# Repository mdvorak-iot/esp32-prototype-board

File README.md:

# esp32-prototype-board

EAGLE schematic for prototype board with 12V power input and all essentials.

Programmed and debugged using [ESP-PROG](https://github.com/espressif/esp-dev-kits/blob/master/esp-prog/docs/ESP-Prog_guide_en.md) interface.

## Renders

</img>

</img>

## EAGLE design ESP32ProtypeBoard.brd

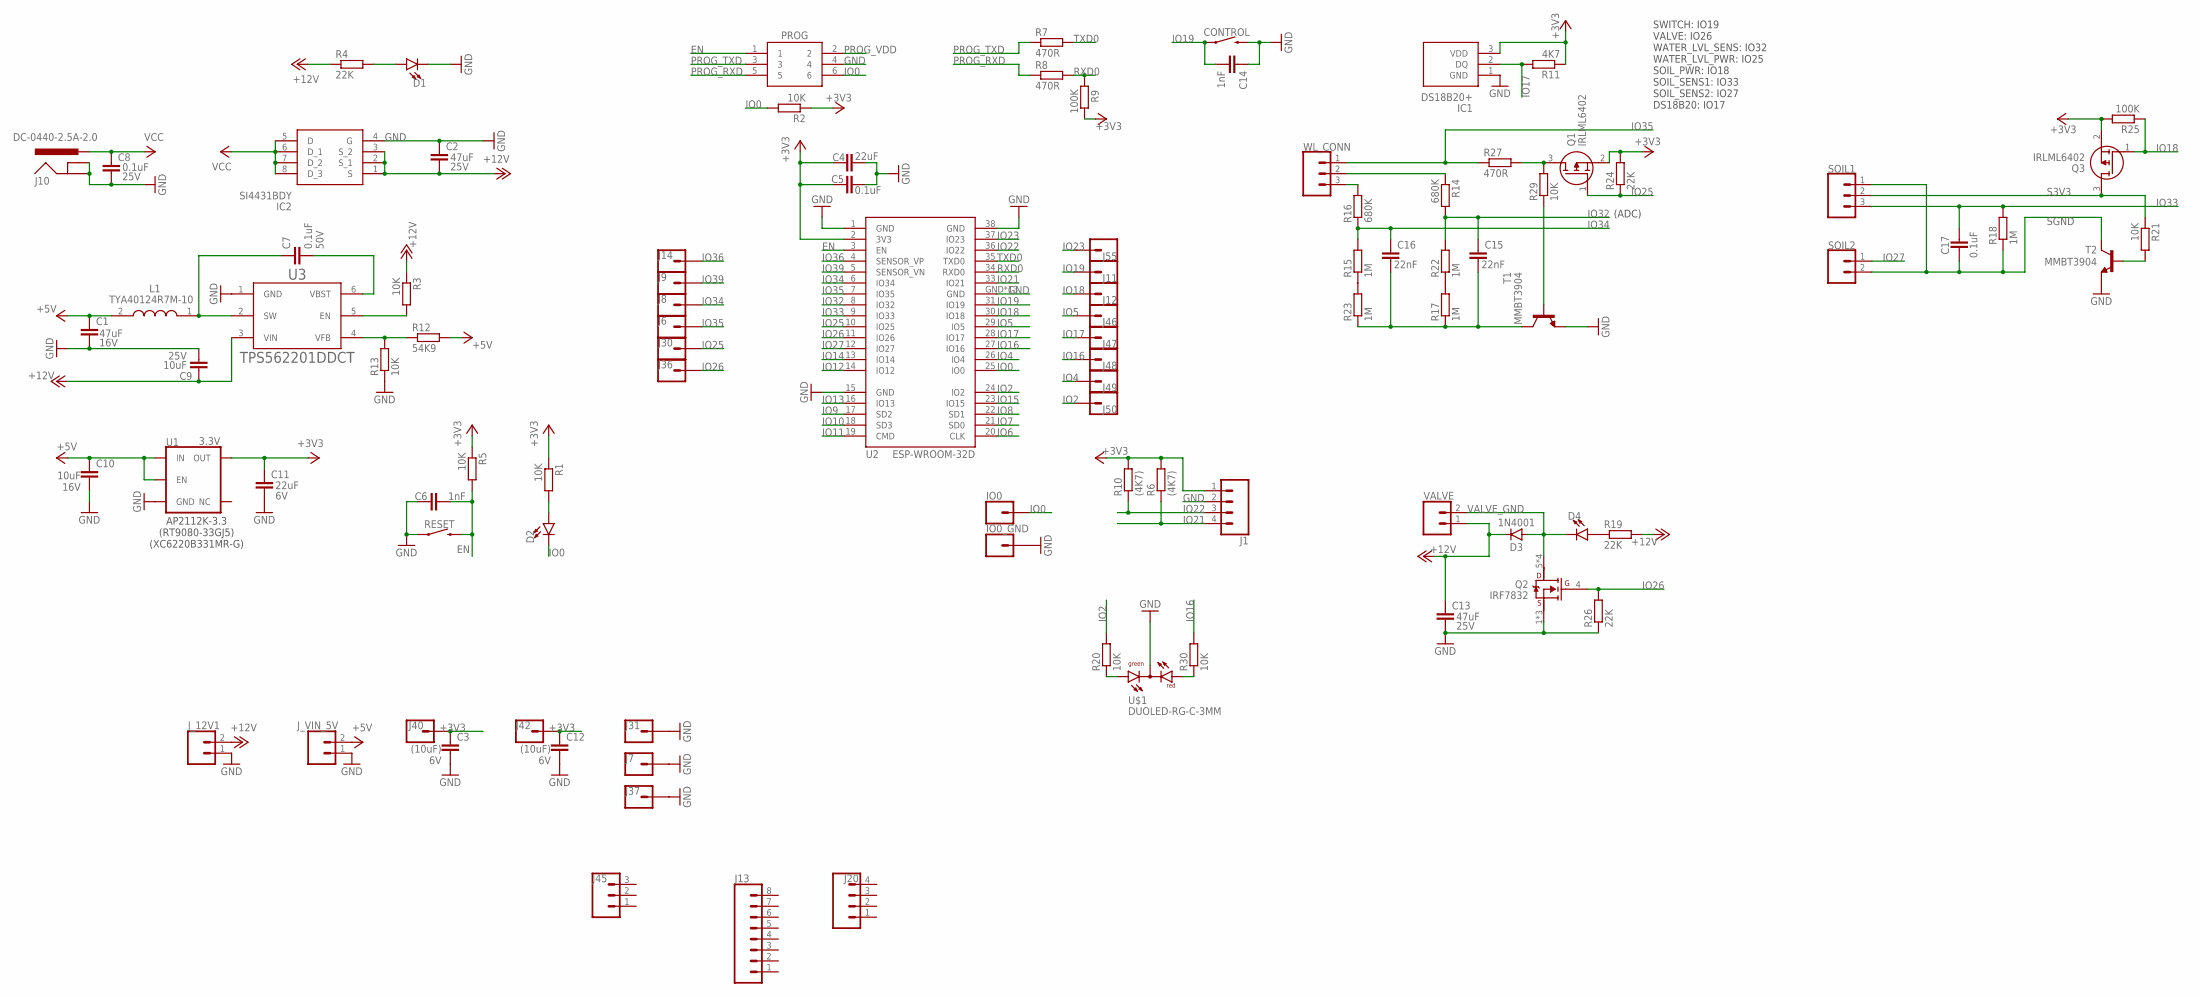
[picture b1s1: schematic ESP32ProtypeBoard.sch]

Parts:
C1: 47uF; C1206K; VOLTAGE 16V
C2, C13: 47uF; C1206K; VOLTAGE 25V
C3, C12: (10uF); C0805K; VOLTAGE 6V
C4: 22uF; C0805K
C5, C17: 0.1uF; C0805K
C6, C14: 1nF; C0805K
C7: 0.1uF; C0805K; VOLTAGE 50V
C8: 0.1uF; C0805K; VOLTAGE 25V
C9: 10uF; C0805K; VOLTAGE 25V
C10: 10uF; C0805K; VOLTAGE 16V
C11: 22uF; C0805K; VOLTAGE 6V
C15, C16: 22nF; C0805K
CONTROL: TACTILE_SIDE_SWITCH_2.5X7X3.5MM
D1: PWR; CHIPLED_0805
D2: GREEN; CHIPLED_0805
D3: 1N4001; DO41-7
D4: VALVE; LED_3MM
IC1: DS18B20+; DS18B20
IC2: SI4431BDY; SOIC127P600X175-8N
IO0: CONN_01PTH_NO_SILK_KIT; 1X01NS_KIT
IO0_GND: CONN_01PTH_NO_SILK_YES_STOP; 1X01_NO_SILK
J1: CONN_04_JSTPH_2.0MM; 1X04_JST_PH_2.0MM
J6, J7, J8, J9, J14, J30, J31, J36, J37, J40, J42: CONN_01_NO_SILK; 1X01_NO_SILK
J10: DC-0440-2.5A-2.0; DC044025A20
J11, J12, J46, J47, J48, J49, J50, J55: CONN_01PTH_NO_SILK_YES_STOP; 1X01_NO_SILK
J13: CONN_08NO_SILK_FEMALE_PTH; 1X08_NO_SILK
J20: CONN_04_NO_SILK; 1X04_NO_SILK
J45: CONN_03_NO_SILK; 1X03_NO_SILK
J_12V1: CONN_021X02_NO_SILK; 1X02_NO_SILK
J_VIN_5V: CONN_021X02_NO_SILK; 1X02_NO_SILK
L1: TYA40124R7M-10; INDPM4040X130N
PROG: DC3-06-1P27
Q1, Q3: IRLML6402; SOT95P237X112-3N
Q2: IRF7832PBF; IRF7832PBF_4
R1, R2, R3, R5, R13, R20, R21, R29, R30: 10K; R0805
R4, R19, R24, R26: 22K; R0805
R6, R10: (4K7); R0805
R7, R8, R27: 470R; R0805
R9, R25: 100K; R0805
R11: 4K7; R0805
R12: 54K9; R0805
R14, R16: 680K; R0805
R15, R17, R18, R22, R23: 1M; R0805
RESET: RESET; TACTILE_SWITCH_SMD_4X3MM
SOIL1: CONN_03_JSTXH_2.54MM_LOCK; 1X03_JST_XH_2.54MM_LOCK
SOIL2: CONN_02_JSTXH_2.54MM_LOCK; 1X02_JST_XH_2.54MM_LOCK
T1, T2: MMBT3904; SOT23-BEC
U1: 3.3V; SOT23-5
U2: ESP-WROOM-32D
U3: TPS562201DDCTTEXAS_INSTRUMENTS_TPS562201DDCT_0_0; TEXAS_INSTRUMENTS_TPS562201DDCT_0
U$1: DUOLED-RG-C-3MM; DUOLED-A-3MM
VALVE: CONN_02_JSTXH_2.54MM_LOCK; 1X02_JST_XH_2.54MM_LOCK
WL_CONN: CONN_03_JSTXH_2.54MM_LOCK; 1X03_JST_XH_2.54MM_LOCK

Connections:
+3V3: C3.1, C4.1, C5.1, C11.1, C12.1, IC1.3 (VDD), J1.1, J40.1, J42.1, Q1.2 (S), Q3.2 (S), R1.1, R2.1, R5.1, R6.2, R9.1, R10.2, R11.1, R24.2, R25.2, U1.5 (OUT), U2.2 (3V3)
+5V: C1.1, C10.1, J_VIN_5V.2, L1.2, R12.2, U1.1 (IN), U1.3 (EN)
+12V: C2.2, C9.1, C13.1, D3.C, IC2.1 (S), IC2.2 (S_1), IC2.3 (S_2), J_12V1.2, R3.1, R4.1, R19.2, U3.3 (VIN), VALVE.1
D2A: D2.A, R1.2
EN: C6.2, PROG.1, R5.2, RESET.2, U2.3 (EN)
GND: C1.2, C2.1, C3.2, C4.2, C5.2, C6.1, C8.2, C9.2, C10.2, C11.2, C12.2, C13.2, C14.1, CONTROL.P$2 (2), D1.C, IC1.1 (GND), IC2.4 (G), IO0_GND.1, J1.2, J7.1, J10.2 (GND), J10.3 (GNDBREAK), J31.1, J37.1, J_12V1.1, J_VIN_5V.1, PROG.4, Q2.1 (1_S), Q2.2 (1_S), Q2.3 (1_S), R13.1, R26.1, RESET.1, T1.E, T2.E, U1.2 (GND), U2.1 (GND), U2.15 (GND), U2.38 (GND), U2.GND, U2.GND_1 (GND), U2.GND_2 (GND), U2.GND_3 (GND), U2.GND_4 (GND), U2.GND_5 (GND), U2.GND_6 (GND), U2.GND_7 (GND), U2.GND_8 (GND), U2.GND_9 (GND), U2.GND_10 (GND), U2.GND_11 (GND), U2.GND_12 (GND), U3.1 (GND), U$1.2 (C)
IO0: D2.C, IO0.1, PROG.6, R2.2, U2.25 (IO0)
IO2: J50.1, R20.2, U2.24 (IO2)
IO4: J49.1, U2.26 (IO4)
IO5: J46.1, U2.29 (IO5)
IO6: U2.20 (CLK)
IO7: U2.21 (SD0)
IO8: U2.22 (SD1)
IO9: U2.17 (SD2)
IO10: U2.18 (SD3)
IO11: U2.19 (CMD)
IO12: U2.14 (IO12)
IO13: U2.16 (IO13)
IO14: U2.13 (IO14)
IO15: U2.23 (IO15)
IO16: J48.1, R30.2, U2.27 (IO16)
IO17: IC1.2 (DQ), J47.1, R11.2, U2.28 (IO17)
IO18: J12.1, Q3.1 (G), R25.1, U2.30 (IO18)
IO19: C14.2, CONTROL.P$1 (1), J11.1, U2.31 (IO19)
IO21: J1.4, R6.1, U2.33 (IO21)
IO22: J1.3, R10.1, U2.36 (IO22)
IO23: J55.1, U2.37 (IO23)
IO25: J30.1, Q1.1 (G), R24.1, U2.10 (IO25)
IO26: J36.1, Q2.4 (G), R26.2, U2.11 (IO26)
IO27: SOIL2.1, U2.12 (IO27)
IO32: C15.1, R14.2, R22.2, U2.8 (IO32)
IO33: C17.2, R18.2, SOIL1.3, U2.9 (IO33)
IO34: C16.1, J8.1, R15.2, R16.1, U2.6 (IO34)
IO35: J6.1, R27.1, U2.7 (IO35), WL_CONN.1
IO36: J14.1, U2.4 (SENSOR_VP)
IO39: J9.1, U2.5 (SENSOR_VN)
unnamed: D4.A, R19.1
unnamed: R15.1, R23.2
unnamed: R20.1, U$1.1 (AG)
unnamed: R30.1, U$1.3 (AR)
unnamed: Q1.3 (D), R27.2, R29.2
unnamed: R17.2, R22.1
unnamed: C15.2, C16.2, R17.1, R23.1, T1.C
unnamed: R21.2, T2.B
PROG_RXD: PROG.5, R8.1
PROG_TXD: PROG.3, R7.1
PROG_VDD: PROG.2
PWR_LED: D1.A, R4.2
RXD0: R8.2, R9.2, U2.34 (RXD0)
S3V3: Q3.3 (D), R21.1, SOIL1.2
SGND: C17.1, R18.1, SOIL1.1, SOIL2.2, T2.C
SW: C7.1, L1.1, U3.2 (SW)
TXD0: R7.2, U2.35 (TXD0)
VALVE_GND: D3.A, D4.K (C), Q2.5 (1_D), Q2.6 (1_D), Q2.7 (1_D), Q2.8 (1_D), VALVE.2
VBST: C7.2, U3.6 (VBST)
VCC: C8.1, IC2.5 (D), IC2.6 (D_1), IC2.7 (D_2), IC2.8 (D_3), J10.1 (PWR)
VEN: R3.2, U3.5 (EN)
VFB: R12.1, R13.2, U3.4 (VFB)
WGND_B: R29.1, T1.B
WL_PROBE: R14.1, WL_CONN.2
WL_SENSE: R16.2, WL_CONN.3

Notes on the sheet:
AP2112K-3.3 (RT9080-33GJ5) (XC6220B331MR-G)
SWITCH: IO19 VALVE: IO26 WATER_LVL_SENS: IO32 WATER_LVL_PWR: IO25 SOIL_PWR: IO18 SOIL_SENS1: IO33 SOIL_SENS2: IO27 DS18B20: IO17
(ADC)

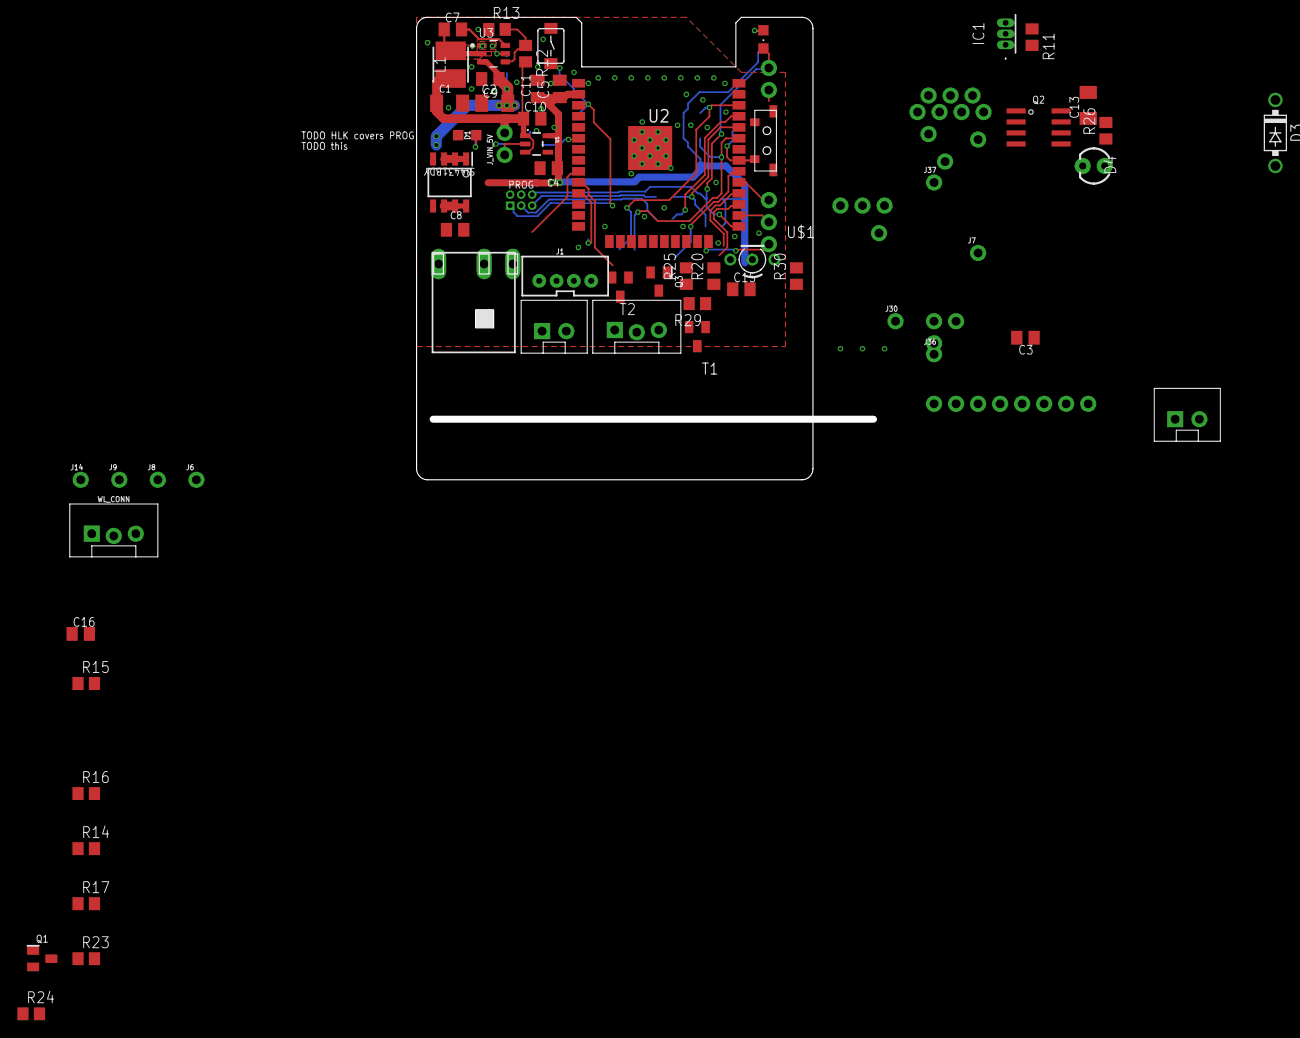
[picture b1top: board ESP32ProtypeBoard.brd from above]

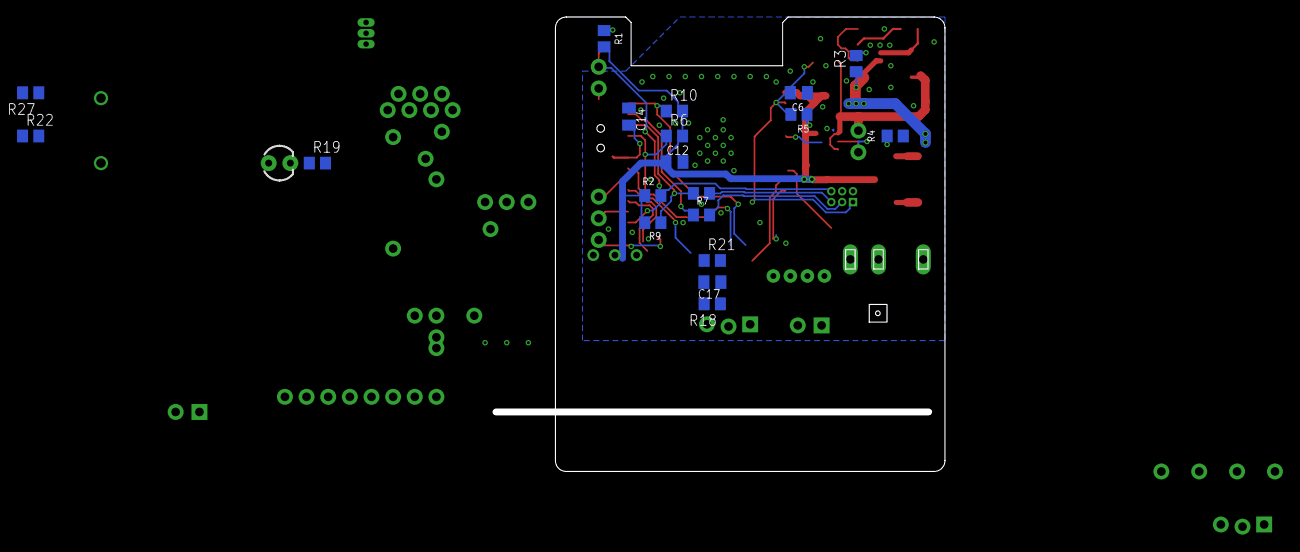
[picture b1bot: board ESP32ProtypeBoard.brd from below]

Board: 2 copper layers, 52.7 x 53.3 mm, 97 parts (19 on the bottom side), 50 nets.

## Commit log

2018-10-29 Project import
2018-10-29 Added libraries (not tested)
2018-10-29 Reorganized rescue pins
2018-10-29 Moved labels
2018-10-29 Reorganizing control pinout
2018-10-29 More complete silk and complete diagram
2018-10-29 Silk about flash modes
2018-10-29 Different flash mode notation
2018-10-29 More silk tuning
2018-10-29 Ignore zips
2018-10-29 Moved npn transistor to bottom
    Moved signature
    Updated libs
2018-10-29 removed stub
2018-10-29 moved mode info text
2018-10-29 removed forgotten pad
2018-10-30 Enlarging fonts
2018-10-30 Bottom silk
2018-10-30 Final silk? maybe
2018-10-31 Finished silk
2018-10-31 Removed hints about reset modes
2018-10-31 Moved IO0 pinout, added pins for easy DS20B18 use
2018-10-31 Final project with electrolytic caps
2018-10-31 22uf cap, pad for gnd
2018-10-31 Smaller pad
2018-11-01 Renamed wierd bottom pins to numbers
2018-11-01 nicer silk
2018-11-01 Completely new layout of the board
2018-11-01 Work in progress on 1.1
2018-11-01 Fixed uart pin order
2018-11-02 All connected
2018-11-02 Moving around some pins
2018-11-02 Fixed silk
2018-11-02 Fixed some stubs
2018-11-02 Replaced VCC IN pins to accomodate large screw terminal
    Some more silk changes
2018-11-02 project
2018-11-02 Final v1.1
2018-11-11 Schema reordered for easier reuse
2019-01-01 Removed main fuse
2019-01-13 Removed long-press flash mode
2019-01-14 Added connections for side empty pins
2019-01-14 Rotated power conn
2019-01-14 Moved controls under ESP
2019-01-14 Improved wiring of power parts a little, reorganized capacitors
2019-01-15 Moved input MOSFET, added pwr diode
2019-01-15 Fixed some silk, improved DTR line, moved EN capacitor
2019-01-15 Moved REG close to ESP to allow very small cutout
2019-01-15 Rewired pins under ESP etc
2019-01-16 Moving around power pins to save space
2019-01-16 Smarter space extra SMD, completed pinout
2019-01-16 FINAL version
    Fixed all silk, moved optional cap
2019-01-21 Slight route adjustments
2019-01-21 Connected gnd
2019-01-23 Replaced holes with large vias
    Larger power trace
    45° corners around antenna
2019-01-26 TODO
2019-01-26 Diode resistors
2019-11-13 Latest EAGLE 9.5.3
2019-12-06 Worked out some TODOs, unfinished board
    LED resistors
    Removed PPTC1
2020-05-15 WIP on next gen
2020-05-15 WIP on new layout
2020-05-15 WIP: almost all essentials wired
2020-05-16 WIP fixed many bugs, added JTAG compatible ordering
2020-05-16 WIP all wired, TODOs left
2020-05-16 Finalizing slowly gen2
2020-05-17 Replaced all 6mil traces with 8mil
    All wired
2020-05-17 Added some silk
2020-05-17 finished some silk
2020-05-17 Fixed outline, removed 2 mount holes, moved them, silk tuning
2020-05-17 Tuned silk, looks ready
2020-05-18 Some more tuning
2020-05-18 Added place for smd capacitor under 220uF electrolytic
    To support at least some cap in space constrained situations
2020-05-18 Smaller caps - 0805K, 1206K layout
2020-05-18 Fixed stub
2020-05-18 Fixed traces under esp (touched gnd), moved cooling vias
    and some more silk tuning
2020-05-19 Switched IO21 and IO0, IO0 is now KIT with covered top side
    Added top silk for all kit holes
    Minor traces improvements
    Stronger GND on the side
2020-05-19 Moved few traces
2020-05-19 added gnd next to 22
2020-05-19 rewired traces around new GND, improved GND routing
    changed polygon width to 8 for wider thermals and less obscure corners
2020-05-19 fixed last 6 wide trace to 8, moved one via to pass gnd
2020-05-19 improved GND routing
    now is both layers completely connected
    improved 3v3 trace as well
2020-05-19 removed stub, now it is valid
2020-05-19 silk pointer
2020-05-19 Added place for smd logic level converter
    used free space
    fixed silk in bottom smd placeholder
2020-05-19 removed extra gnd, added dot as orientation mark
2020-05-19 minor tuning
2020-05-19 moved vias to improve text readability
2020-06-01 Update README.md
    TODOs
2020-06-02 added JTAG special labels
2020-06-08 Moved AC in a little more apart
2021-05-01 Initial gen3 commit
2021-05-01 Removed input 220uF cap (should work without)
2021-05-01 Replaced buck converter module with custom curcuit
    Using ACT4088US-T for 5V rail
2021-05-01 Replaced all resistors with 0805 variants
2021-05-01 Making layout smaller
2021-05-01 Placed power curcuit for now
2021-05-01 Using esp-prog as programming interface
    Removed RTS/DTS reset boot logic
2021-05-01 some wiring
2021-05-02 Replaced switch, fixed errors
2021-05-02 small tuning
2021-05-02 added voltage attribute to some caps
2021-05-05 Experimenting with another layout: reset in middle
2021-05-05 Replaced leds with 0805
2021-05-05 Moved PROG to right side
2021-05-14 replaced LDO with RT9080-33GJ5 (smaller)
    more expensive, only 600mA
    better buck converter position
2021-05-15 using cheaper LDO, added some traces
2021-05-15 A lot of wirings, no terminals in place yet
    Power cascade looks good
2021-05-15 added missing 3v3 connection
2021-05-15 added missing FB connection
2021-05-15 Fixed terminal position, improved gnd traces
2021-05-15 12V pin
2021-05-15 first data lines, added new VIN pin closer
2021-05-15 rerouted EN to bottom
2021-05-15 3v3 trace extended to left
2021-05-15 two more pins and 3v3 pin
2021-05-15 placed unrouted jtag
2021-05-15 routed jtag
2021-05-15 much better jtag routing
2021-05-15 few more pins
2021-05-15 I2C pins at right side, tuning
2021-05-15 moved vcc hole
2021-05-16 added unrouted all gpio
2021-05-16 removed gnd from right upper corner
2021-05-16 led via
2021-05-16 moved all gpios a little down to fit below esp
2021-05-16 fixed traces and silk after move
2021-05-16 details
2021-05-16 experiments with layout
2021-05-16 working on dedicated jtag 1.27mm
2021-05-16 working on new traces
2021-05-16 all traces connected
2021-05-16 fixed some errors
2021-05-16 ignore lbr historical files
2021-05-16 added my-connectors.lbr
2021-05-16 created place for HLK AC converter
2021-05-16 silk, tuning
2021-05-16 improved gnd plane connection
2021-05-16 added more empty pads
2021-05-16 removed gnd plain from breadboard on left side
2021-05-16 more improvements
2021-05-16 removed header names
2021-05-16 slight improvements
2021-05-16 moved HLK to bottom
2021-05-16 added sot-23 placeholder under jtag
2021-05-16 flipped HLK pads
2021-05-16 flixed DRC
2021-05-16 silk tuning
2021-05-16 added bottom silk
2021-05-16 added some top silk
2021-05-16 completed top silk
2021-05-16 detailing
2021-05-16 signal smoothing
2021-05-16 improved a little bottom gnd plane
2021-05-16 missing silk line
2021-05-17 added optional 3V3 capacitors
2021-05-17 added thru hole for inductor soldering
2021-05-17 fixed corner dimensions
2021-05-17 silk
2021-05-17 added PPTC for 3V3 terminals
2021-05-18 added gnd next to vin
2021-05-18 minor gnd tuning
2021-05-18 nicer silk around esp
2021-05-18 final silk touches
2021-05-18 added renders
2021-05-18 Added alternative LDO type
2021-06-16 New ESP-WROOM-32D/E layout
2021-06-16 Improved TPS562201DDCTT lbr, using it in design
    WIP: Schematic only, no layout yet
2021-06-16 Removed restrict from TPS562201 lbr
    WIP: converter layout
2021-06-16 Added custom modified DC-044 power jack
2021-06-16 WIP: new layout
2021-06-17 Added no-silk longpad connector
2021-06-17 Wired new DCDC converter
2021-06-17 Layout tuning
2021-06-17 Connected moved pins, moved bottom silk
2021-06-17 Moved breadboard one step down
    making more space between wroom and pins
    silk fits better
2021-06-17 Added restrict to DC jack footprint
2021-06-17 silk for sot8 placeholder
2021-06-17 Removed bss138 placeholder, moved IO27 to left
    Created space for DS18B20
    Moved IO25 and 26 one place left
2021-06-17 Moved IO32 and 33 one place left
2021-06-17 moved IO18 down
2021-06-18 added gnd to right
2021-06-18 added pull-ups to I2C and IO27, pull downs and capacitors to ADC
2021-06-18 removed PPTC for 3V3 out
    using rail directly, hopefully LDO will handle short curcuit
2021-06-18 WIP: ADC pull downs and caps layout
2021-06-21 wired ADC caps
2021-06-21 Improved ADC caps layout, improved GND plane around
2021-06-21 Fixed silk for all placed components
2021-06-21 Turned DC jack connector facing up again
    It was non-sense to face it cut-out side
    Historically all versions had it facing top
    Adjusted everything around
2021-06-21 increased power via drill
    removed stubs
2021-06-21 added some vias, improved layout slightly
2021-06-21 first irrigation board modifications
    added DS18B20 lbr
    added DS18B20 to board instead of generic pins
2021-06-23 added IRF7832 lbr, more irrigation components
2021-06-23 WIP: layout
2021-06-23 improved layout for smd connections
    use 90 degree angles only
2021-06-23 better pwr trace
2021-06-23 removed adc resistors
2021-06-23 improved layout across the board
    avoid acute trace angles for pads
2021-06-23 added optional RD18 (pull down IO18)
2021-06-23 improving layout
2021-06-24 added custom 1N4001 component
2021-06-24 fake 5pin conn silk
2021-06-24 added missed 1N4001.lbr
    some layout changes
2021-06-24 moved pwr trace a little
2021-06-25 improved my-connectors.lbr - added JST XH
    removed separate device for 1.27mm footprints
2021-06-25 fixed JST XH connectors, renamed symbol in connectors
2021-06-25 more tuning of my-connectors
2021-06-25 added JST XH variants up to 5 pins
2021-06-25 added new jst connector to water levels
2021-06-25 updated my-connectors.lbr
    added JST variants
    removed 1.27mm devices, using just packages
2021-06-25 more components and layout
2021-06-26 WIP: layout, added cap for IO19
    new cap is for another custom switch
2021-06-26 added extra optional cap for IO19
    for addditional switch for SW reset
2021-06-26 removed custom libs (moving to submodule)
2021-06-26 added lbr submodule
2021-06-26 removed local libs
2021-06-26 added lbr submodule, fixed used libraries paths
2021-07-01 dded sensor components
2021-07-02 updated lbr
2021-07-02 added p-mosfet for sensor power, unified water and soil sensors
2021-07-07 two-pin water level sensor, fets to turn off soil hum sensor completely
2021-07-08 updated lbr, use AO3400 as N-MOSFET
2021-07-08 working on layout
2021-07-08 water level sensor layout
2021-07-08 layout cleanup
2021-07-09 NPN to disconnect GND on water sensor
2021-07-09 use mmbt3904 to disconnect WGND
2021-07-20 updates to layout and schema - updated pinout
2021-07-22 fixed sensor pinout
2021-07-23 increased water level capacitor
2021-07-24 WL cap set to 22nF, 470R resistor moved to IO32 pin
2021-07-29 reworking layout and pinout, soil sensors
2021-08-01 added status led
2021-08-02 moved everything to left to make more space for switch etc
2021-08-05 replaced water sensor connector with pads
2022-08-03 Moved water sensor to seaprate file
2022-08-03 added info about sensor connections
2022-08-12 moving toward real schema

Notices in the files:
ESP32ProtypeBoard.brd:
Mikee © 2021/06 v3.1
parts and their libraries:
SparkFun-Connectors: Licensing: Creative Commons ShareAlike 4.0 International - https://creativecommons.org/licenses/by-sa/4.0
esp32-modified: Creative Commons Attribution-ShareAlike 4.0 International
